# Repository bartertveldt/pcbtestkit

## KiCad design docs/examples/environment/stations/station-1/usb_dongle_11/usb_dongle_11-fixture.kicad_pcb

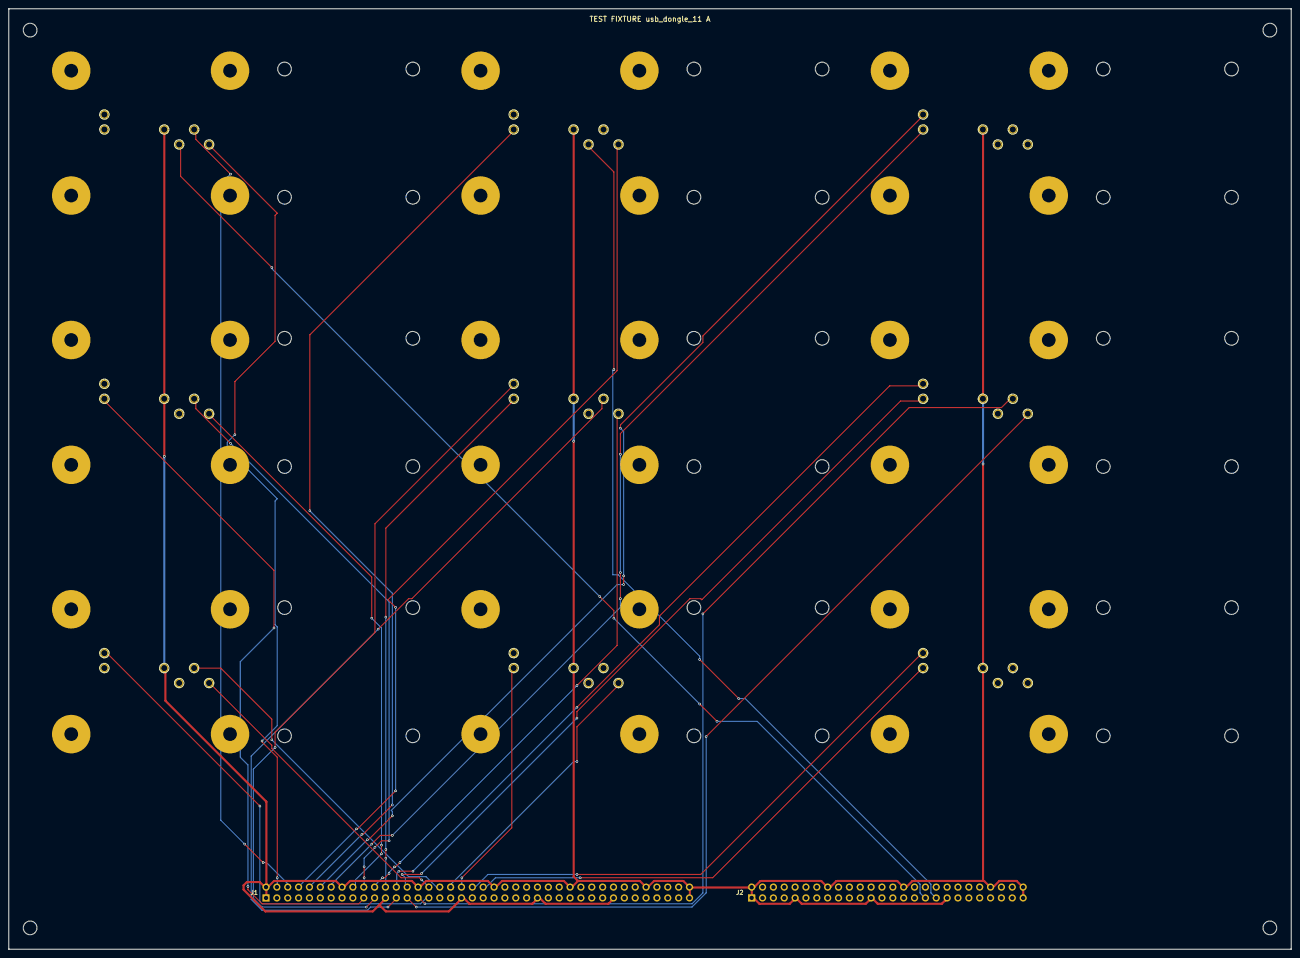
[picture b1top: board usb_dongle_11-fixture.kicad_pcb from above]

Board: 2 copper layers, 300.0 x 220.0 mm, 150 parts (0 on the bottom side), 39 nets.

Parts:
H1, H2, H3, H4: M3; MountingHole_3.2mm
J1: J1; PinHeader_2x40_P2.54mm_Vertical
J2: J2; PinHeader_2x26_P2.54mm_Vertical
K1, K2, K3, K4, K5, K6, K7, K8, K9: TOGGLE CLAMP; ToggleClamp
N1, N2, N3, N4, N5, N6, N7, N8, N9: NEST; Nest
NK1, NK2, NK3, NK4, NK5, NK6, NK7, NK8, NK9, NK10, NK11, NK12, NK13, NK14, NK15, NK16, NK17, NK18, NK19, NK20, NK21, NK22, NK23, NK24, NK25, NK26, NK27, NK28, NK29, NK30, NK31, NK32, NK33, NK34, NK35, NK36: CLAMP M3; ClampScrew_M3
NP1, NP2, NP3, NP4, NP5, NP6, NP7, NP8, NP9, NP10, NP11, NP12, NP13, NP14, NP15, NP16, NP17, NP18, NP19, NP20, NP21, NP22, NP23, NP24, NP25, NP26, NP27, NP28, NP29, NP30, NP31, NP32, NP33, NP34, NP35, NP36: STANDOFF M3; NestPost_M3
P1, P7, P13, P19, P25, P31, P37, P43, P49: GND; Pogo_P75_receptacle
P2, P8, P14, P20, P26, P32, P38, P44, P50: +3V3; Pogo_P75_receptacle
P3, P9, P15, P21, P27, P33, P39, P45, P51: VBUS; Pogo_P75_receptacle
P4, P10, P16, P22, P28, P34, P40, P46, P52: SWCLK; Pogo_P75_receptacle
P5, P11, P17, P23, P29, P35, P41, P47, P53: SWDIO; Pogo_P75_receptacle
P6, P12, P18, P24, P30, P36, P42, P48, P54: USB_D+; Pogo_P75_receptacle

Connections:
GND: J1.1 (GND), J1.2 (GND), J1.9 (GND), J1.16 (GND), J1.23 (GND), J1.30 (GND), J1.37 (GND), J1.44 (GND), J1.51 (GND), J1.58 (GND), J1.65 (GND), J1.72 (GND), J1.79 (GND), J1.80 (GND), J2.1 (GND), J2.2 (GND), J2.9 (GND), J2.16 (GND), J2.23 (GND), J2.30 (GND), J2.37 (GND), J2.46 (GND), J2.51 (GND), J2.52 (GND), P1.1, P7.1, P13.1, P19.1, P25.1, P31.1, P37.1, P43.1, P49.1
S1_TP_+3V3: J1.3 (AIN1), P2.1
S1_TP_SWCLK: J1.5 (AIN3), P4.1
S1_TP_SWDIO: J1.6 (AIN4), P5.1
S1_TP_USB_D+: J2.33 (USB_DP), P6.1
S1_TP_VBUS: J1.4 (AIN2), P3.1
S2_TP_+3V3: J1.7 (AIN5), P8.1
S2_TP_SWCLK: J1.10 (AIN7), P10.1
S2_TP_SWDIO: J1.11 (AIN8), P11.1
S2_TP_USB_D+: J2.35 (USB2_DP), P12.1
S2_TP_VBUS: J1.8 (AIN6), P9.1
S3_TP_+3V3: J1.12 (AIN9), P14.1
S3_TP_SWCLK: J1.14 (AIN11), P16.1
S3_TP_SWDIO: J1.15 (AIN12), P17.1
S3_TP_VBUS: J1.13 (AIN10), P15.1
S4_TP_+3V3: J1.17 (AIN13), P20.1
S4_TP_SWCLK: J1.19 (AIN15), P22.1
S4_TP_SWDIO: J1.20 (AIN16), P23.1
S4_TP_VBUS: J1.18 (AIN14), P21.1
S5_TP_+3V3: J1.21 (AIN17), P26.1
S5_TP_SWCLK: J1.24 (AIN19), P28.1
S5_TP_SWDIO: J1.25 (AIN20), P29.1
S5_TP_VBUS: J1.22 (AIN18), P27.1
S6_TP_+3V3: J1.26 (AIN21), P32.1
S6_TP_SWCLK: J1.28 (AIN23), P34.1
S6_TP_SWDIO: J1.29 (AIN24), P35.1
S6_TP_VBUS: J1.27 (AIN22), P33.1
S7_TP_+3V3: J1.31 (AIN25), P38.1
S7_TP_SWCLK: J1.33 (AIN27), P40.1
S7_TP_SWDIO: J1.34 (AIN28), P41.1
S7_TP_VBUS: J1.32 (AIN26), P39.1
S8_TP_+3V3: J1.35 (AIN29), P44.1
S8_TP_SWCLK: J1.38 (AIN31), P46.1
S8_TP_SWDIO: J1.39 (AIN32), P47.1
S8_TP_VBUS: J1.36 (AIN30), P45.1
S9_TP_+3V3: J1.40 (AIN33), P50.1
S9_TP_SWCLK: J1.42 (AIN35), P52.1
S9_TP_SWDIO: J1.43 (AIN36), P53.1
S9_TP_VBUS: J1.41 (AIN34), P51.1

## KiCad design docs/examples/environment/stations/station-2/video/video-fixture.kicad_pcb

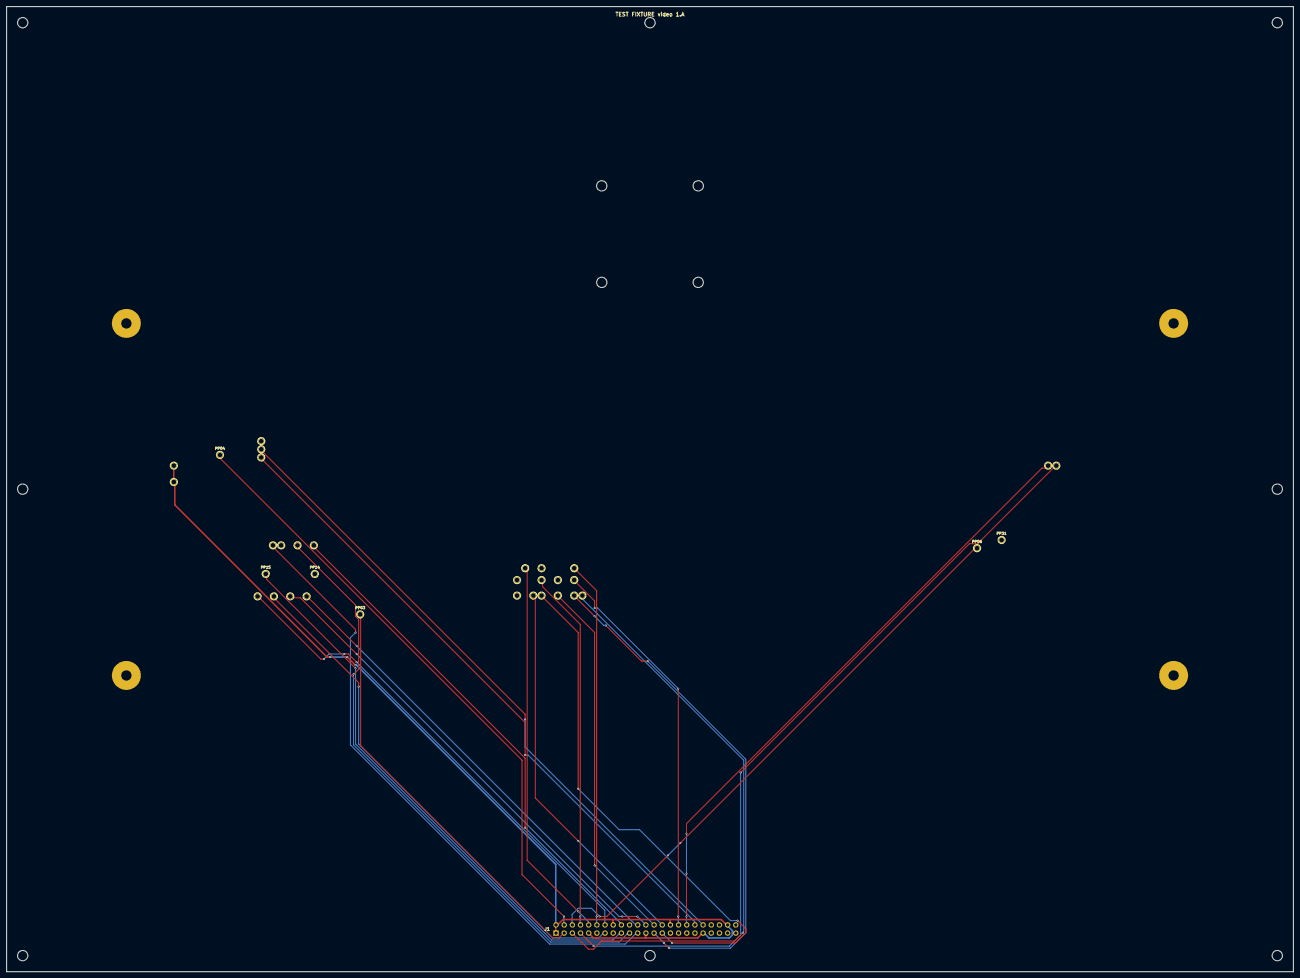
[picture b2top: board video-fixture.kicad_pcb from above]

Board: 2 copper layers, 400.0 x 300.0 mm, 53 parts (0 on the bottom side), 33 nets.

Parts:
H1, H2, H3, H4, H5, H6, H7, H8: M3; MountingHole_3.2mm
J1: J1; PinHeader_2x23_P2.54mm_Vertical
K1: TOGGLE CLAMP; ToggleClamp
N1: NEST; Nest
NK1, NK2, NK3, NK4: CLAMP M3; ClampScrew_M3
NP1, NP2, NP3, NP4: STANDOFF M3; NestPost_M3
P1, P2: GND; Pogo_P75_receptacle
P3: +3.3V; Pogo_P75_receptacle
P4: +5F; Pogo_P75_receptacle
P5: +5V; Pogo_P75_receptacle
P6: VAA; Pogo_P75_receptacle
P7: BLANK-; Pogo_P75_receptacle
P8: EA1; Pogo_P75_receptacle
P9: EA2; Pogo_P75_receptacle
P10: EA3; Pogo_P75_receptacle
P11: EA4; Pogo_P75_receptacle
P12: EA5; Pogo_P75_receptacle
P13: EA6; Pogo_P75_receptacle
P14: EA7; Pogo_P75_receptacle
P15: EA9; Pogo_P75_receptacle
P16: EA10; Pogo_P75_receptacle
P17: EA11; Pogo_P75_receptacle
P18: EA12; Pogo_P75_receptacle
P19: EA13; Pogo_P75_receptacle
P20: EA14; Pogo_P75_receptacle
P21: EA15; Pogo_P75_receptacle
P22: EQ0; Pogo_P75_receptacle
P23: EQ1; Pogo_P75_receptacle
P24: EQ2; Pogo_P75_receptacle
P25: EQ3; Pogo_P75_receptacle
P26: EQ4; Pogo_P75_receptacle
P27: EQ5; Pogo_P75_receptacle
P28: EQ6; Pogo_P75_receptacle
P29: EQ7; Pogo_P75_receptacle
P30: CLKCDA; Pogo_P75_receptacle
P31: CSYNCIN-; Pogo_P75_receptacle
P32: DQ8; Pogo_P75_receptacle
P33: DQ9; Pogo_P75_receptacle
P34: DQ10; Pogo_P75_receptacle

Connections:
GND: J1.1 (GND), J1.2 (GND), J1.9 (GND), J1.16 (GND), J1.23 (GND), J1.30 (GND), J1.37 (GND), J1.44 (GND), J1.45 (GND), P1.1, P2.1
TP_+3.3V: J1.3 (AIN1), P3.1
TP_+5F: J1.4 (AIN2), P4.1
TP_+5V: J1.5 (AIN3), P5.1
TP_BLANK-: J1.7 (AIN5), P7.1
TP_CLKCDA: J1.34 (AIN28), P30.1
TP_CSYNCIN-: J1.35 (AIN29), P31.1
TP_DQ8: J1.36 (AIN30), P32.1
TP_DQ9: J1.38 (AIN31), P33.1
TP_DQ10: J1.39 (AIN32), P34.1
TP_EA1: J1.8 (AIN6), P8.1
TP_EA2: J1.10 (AIN7), P9.1
TP_EA3: J1.11 (AIN8), P10.1
TP_EA4: J1.12 (AIN9), P11.1
TP_EA5: J1.13 (AIN10), P12.1
TP_EA6: J1.14 (AIN11), P13.1
TP_EA7: J1.15 (AIN12), P14.1
TP_EA9: J1.17 (AIN13), P15.1
TP_EA10: J1.18 (AIN14), P16.1
TP_EA11: J1.19 (AIN15), P17.1
TP_EA12: J1.20 (AIN16), P18.1
TP_EA13: J1.21 (AIN17), P19.1
TP_EA14: J1.22 (AIN18), P20.1
TP_EA15: J1.24 (AIN19), P21.1
TP_EQ0: J1.25 (AIN20), P22.1
TP_EQ1: J1.26 (AIN21), P23.1
TP_EQ2: J1.27 (AIN22), P24.1
TP_EQ3: J1.28 (AIN23), P25.1
TP_EQ4: J1.29 (AIN24), P26.1
TP_EQ5: J1.31 (AIN25), P27.1
TP_EQ6: J1.32 (AIN26), P28.1
TP_EQ7: J1.33 (AIN27), P29.1
TP_VAA: J1.6 (AIN4), P6.1

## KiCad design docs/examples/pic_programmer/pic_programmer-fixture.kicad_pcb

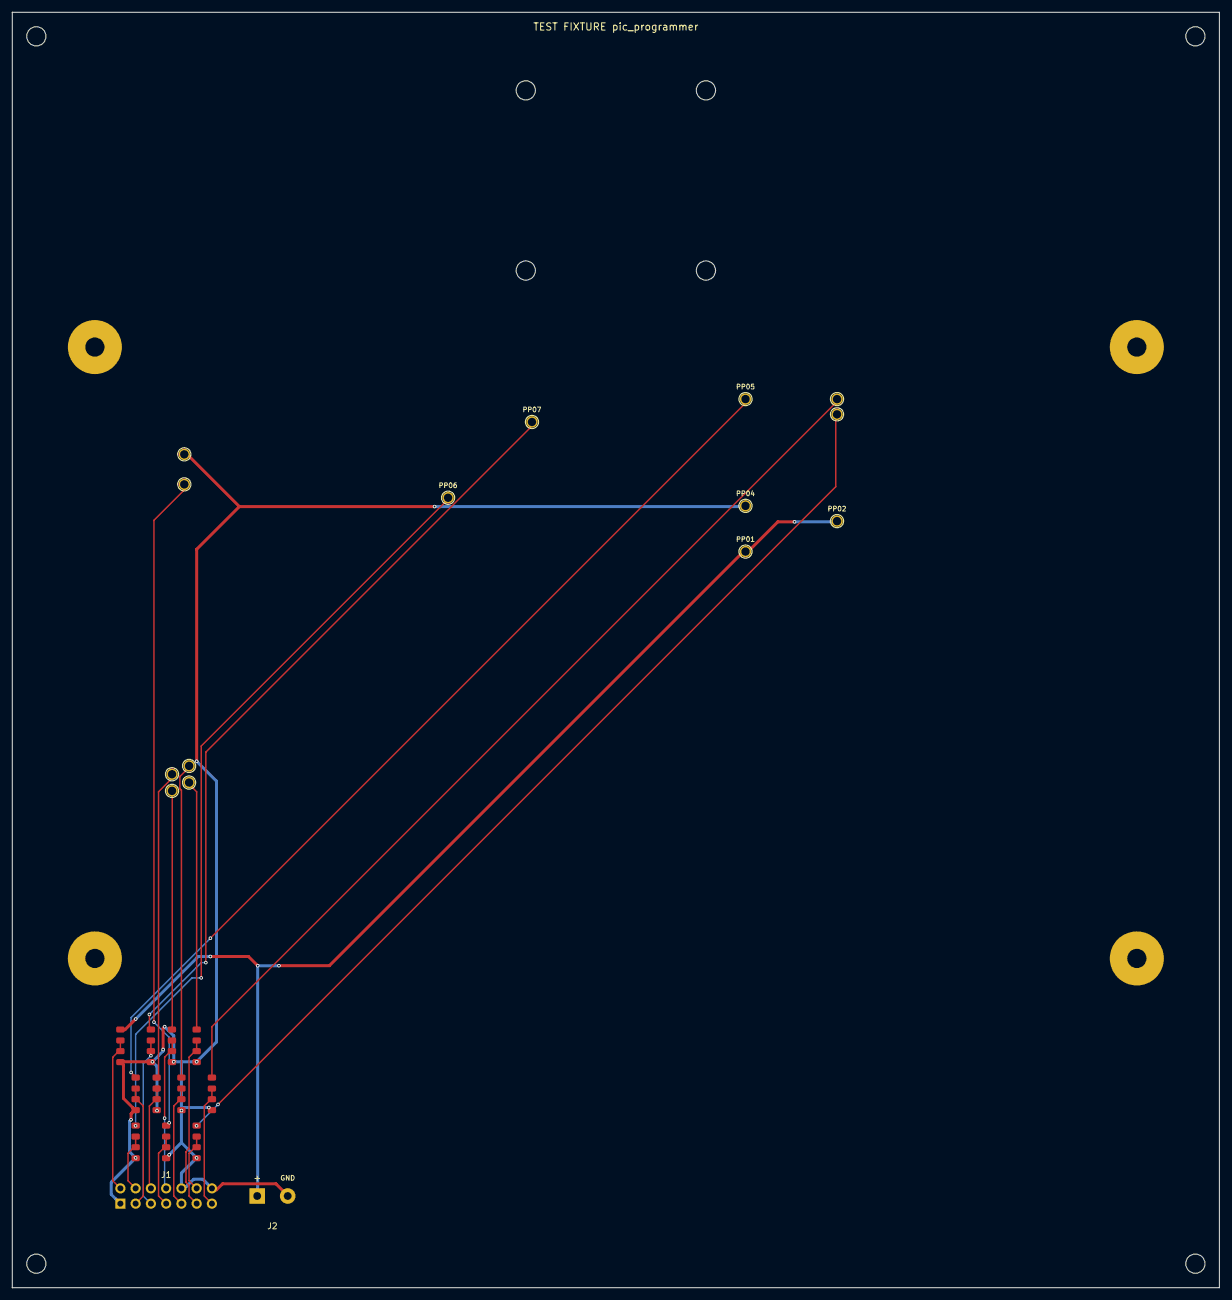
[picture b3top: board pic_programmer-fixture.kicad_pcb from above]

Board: 2 copper layers, 201.0 x 212.4 mm, 52 parts (0 on the bottom side), 23 nets.

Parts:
H1, H2, H3, H4: M3 standoff; MountingHole_3.2mm
J1: TEST_IO; PinHeader_2x07_P2.54mm_Vertical
J2: DUT_POWER; TerminalBlock_bornier-2_P5.08mm
K1: TOGGLE CLAMP; ToggleClamp
N1: NEST; Nest
NK1, NK2, NK3, NK4: CLAMP M3; ClampScrew_M3
NP1, NP2, NP3, NP4: STANDOFF M3; NestPost_M3
P1, P2: VCC_PIC; Pogo_P75_receptacle
P3, P4: GND; Pogo_P75_receptacle
P5: VPP{slash}MCLR; Pogo_P75_receptacle
P6: VCC; Pogo_P75_receptacle
P7: VPP; Pogo_P75_receptacle
P8: PC-DATA-IN; Pogo_P75_receptacle
P9: Net-(D1-A); Pogo_P75_receptacle
P10: PC-CLOCK-OUT; Pogo_P75_receptacle
P11: PC-DATA-OUT; Pogo_P75_receptacle
P12: VPP_ON; Pogo_P75_receptacle
P13: CLOCK-RB6; Pogo_P75_receptacle
P14: DATA-RB7; Pogo_P75_receptacle
R1, R3, R5, R7: 1.2k; R_0805_2012Metric
R2, R4, R6, R8: 10k; R_0805_2012Metric
R9, R11, R13, R15, R17, R19, R21: 12k; R_0805_2012Metric
R10, R12, R14, R16, R18, R20, R22: 100k; R_0805_2012Metric

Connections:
CH01: J1.2 (CH01), R1.1, R2.2
CH02: J1.3 (CH02), R3.1, R4.2
CH03: J1.4 (CH03), R5.1, R6.2
CH04: J1.5 (CH04), R7.1, R8.2
CH05: J1.6 (CH05), R9.1, R10.2
CH06: J1.7 (CH06), R11.1, R12.2
CH07: J1.8 (CH07), R13.1, R14.2
CH08: J1.9 (CH08), R15.1, R16.2
CH09: J1.11 (CH09), R17.1, R18.2
CH10: J1.12 (CH10), R19.1, R20.2
CH11: J1.13 (CH11), R21.1, R22.2
GND: J1.1 (GND), J1.10 (GND), J1.14 (GND), J2.2 (GND), P3.1, P4.1, R2.1, R4.1, R6.1, R8.1, R10.1, R12.1, R14.1, R16.1, R18.1, R20.1, R22.1
TP_CLOCK-RB6: P13.1, R19.2
TP_DATA-RB7: P14.1, R21.2
TP_Net-_D1-A: P9.1, R11.2
TP_PC-CLOCK-OUT: P10.1, R13.2
TP_PC-DATA-IN: P8.1, R9.2
TP_PC-DATA-OUT: P11.1, R15.2
TP_VCC: P6.1, R5.2
TP_VPP: P7.1, R7.2
TP_VPP_ON: P12.1, R17.2
TP_VPP_slash_MCLR: P5.1, R3.2
VIN: J2.1 (VIN), P1.1, P2.1, R1.2

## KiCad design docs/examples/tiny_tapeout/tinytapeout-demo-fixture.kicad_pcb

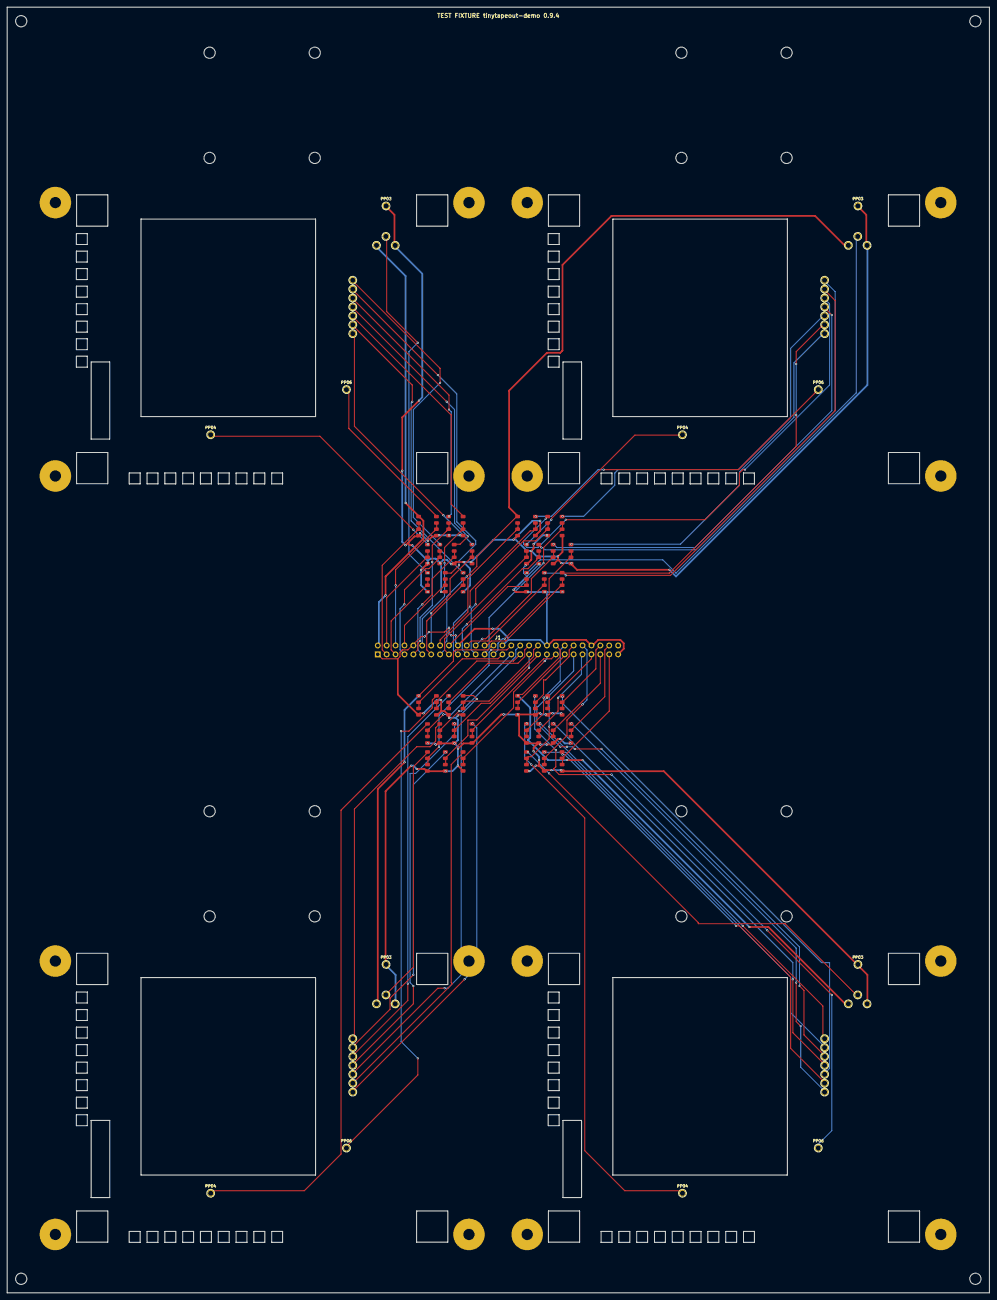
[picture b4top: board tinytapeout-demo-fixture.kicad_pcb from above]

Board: 2 copper layers, 280.2 x 366.8 mm, 185 parts (0 on the bottom side), 89 nets.

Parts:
H1, H2, H3, H4: M3 standoff; MountingHole_3.2mm
J1: TEST_IO; PinHeader_2x28_P2.54mm_Vertical
K1, K2, K3, K4: TOGGLE CLAMP; ToggleClamp
N1, N2, N3, N4: NEST; Nest
NK1, NK2, NK3, NK4, NK5, NK6, NK7, NK8, NK9, NK10, NK11, NK12, NK13, NK14, NK15, NK16: CLAMP M3; ClampScrew_M3
NP1, NP2, NP3, NP4, NP5, NP6, NP7, NP8, NP9, NP10, NP11, NP12, NP13, NP14, NP15, NP16: STANDOFF M3; NestPost_M3
P1, P14, P27, P40: VBUS; Pogo_P75_receptacle
P2, P3, P15, P16, P28, P29, P41, P42: GND; Pogo_P75_receptacle
P4, P17, P30, P43: +3V3; Pogo_P75_receptacle
P5, P18, P31, P44: +5V; Pogo_P75_receptacle
P6, P19, P32, P45: DVDD; Pogo_P75_receptacle
P7, P20, P33, P46: in1; Pogo_P75_receptacle
P8, P21, P34, P47: in2; Pogo_P75_receptacle
P9, P22, P35, P48: in3; Pogo_P75_receptacle
P10, P23, P36, P49: in4; Pogo_P75_receptacle
P11, P24, P37, P50: in5; Pogo_P75_receptacle
P12, P25, P38, P51: in6; Pogo_P75_receptacle
P13, P26, P39, P52: in7; Pogo_P75_receptacle
R1, R5, R7, R23, R27, R29, R45, R49, R51, R67, R71, R73: 8.2k; R_0805_2012Metric
R2, R4, R6, R8, R24, R26, R28, R30, R46, R48, R50, R52, R68, R70, R72, R74: 10k; R_0805_2012Metric
R3, R25, R47, R69: 1.8k; R_0805_2012Metric
R9, R11, R13, R15, R17, R19, R21, R31, R33, R35, R37, R39, R41, R43, R53, R55, R57, R59, R61, R63, R65, R75, R77, R79, R81, R83, R85, R87: 82k; R_0805_2012Metric
R10, R12, R14, R16, R18, R20, R22, R32, R34, R36, R38, R40, R42, R44, R54, R56, R58, R60, R62, R64, R66, R76, R78, R80, R82, R84, R86, R88: 100k; R_0805_2012Metric

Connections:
GND: J1.1 (GND), J1.10 (GND), J1.20 (GND), J1.30 (GND), J1.40 (GND), J1.50 (GND), J1.55 (GND), P2.1, P3.1, P15.1, P16.1, P28.1, P29.1, P41.1, P42.1, R2.1, R4.1, R6.1, R8.1, R10.1, R12.1, R14.1, R16.1, R18.1, R20.1, R22.1, R24.1, R26.1, R28.1, R30.1, R32.1, R34.1, R36.1, R38.1, R40.1, R42.1, R44.1, R46.1, R48.1, R50.1, R52.1, R54.1, R56.1, R58.1, R60.1, R62.1, R64.1, R66.1, R68.1, R70.1, R72.1, R74.1, R76.1, R78.1, R80.1, R82.1, R84.1, R86.1, R88.1
S1_CH01: J1.3 (S1 CH01), R1.1, R2.2
S1_CH02: J1.4 (S1 CH02), R3.1, R4.2
S1_CH03: J1.5 (S1 CH03), R5.1, R6.2
S1_CH04: J1.6 (S1 CH04), R7.1, R8.2
S1_CH05: J1.7 (S1 CH05), R9.1, R10.2
S1_CH06: J1.8 (S1 CH06), R11.1, R12.2
S1_CH07: J1.9 (S1 CH07), R13.1, R14.2
S1_CH08: J1.11 (S1 CH08), R15.1, R16.2
S1_CH09: J1.12 (S1 CH09), R17.1, R18.2
S1_CH10: J1.13 (S1 CH10), R19.1, R20.2
S1_CH11: J1.14 (S1 CH11), R21.1, R22.2
S1_TP_+3V3: P4.1, R3.2
S1_TP_+5V: P5.1, R5.2
S1_TP_DVDD: P6.1, R7.2
S1_TP_in1: P7.1, R9.2
S1_TP_in2: P8.1, R11.2
S1_TP_in3: P9.1, R13.2
S1_TP_in4: P10.1, R15.2
S1_TP_in5: P11.1, R17.2
S1_TP_in6: P12.1, R19.2
S1_TP_in7: P13.1, R21.2
S1_VIN: J1.2 (S1 VIN), P1.1, R1.2
S2_CH01: J1.16 (S2 CH01), R23.1, R24.2
S2_CH02: J1.17 (S2 CH02), R25.1, R26.2
S2_CH03: J1.18 (S2 CH03), R27.1, R28.2
S2_CH04: J1.19 (S2 CH04), R29.1, R30.2
S2_CH05: J1.21 (S2 CH05), R31.1, R32.2
S2_CH06: J1.22 (S2 CH06), R33.1, R34.2
S2_CH07: J1.23 (S2 CH07), R35.1, R36.2
S2_CH08: J1.24 (S2 CH08), R37.1, R38.2
S2_CH09: J1.25 (S2 CH09), R39.1, R40.2
S2_CH10: J1.26 (S2 CH10), R41.1, R42.2
S2_CH11: J1.27 (S2 CH11), R43.1, R44.2
S2_TP_+3V3: P17.1, R25.2
S2_TP_+5V: P18.1, R27.2
S2_TP_DVDD: P19.1, R29.2
S2_TP_in1: P20.1, R31.2
S2_TP_in2: P21.1, R33.2
S2_TP_in3: P22.1, R35.2
S2_TP_in4: P23.1, R37.2
S2_TP_in5: P24.1, R39.2
S2_TP_in6: P25.1, R41.2
S2_TP_in7: P26.1, R43.2
S2_VIN: J1.15 (S2 VIN), P14.1, R23.2
S3_CH01: J1.29 (S3 CH01), R45.1, R46.2
S3_CH02: J1.31 (S3 CH02), R47.1, R48.2
S3_CH03: J1.32 (S3 CH03), R49.1, R50.2
S3_CH04: J1.33 (S3 CH04), R51.1, R52.2
S3_CH05: J1.34 (S3 CH05), R53.1, R54.2
S3_CH06: J1.35 (S3 CH06), R55.1, R56.2
S3_CH07: J1.36 (S3 CH07), R57.1, R58.2
S3_CH08: J1.37 (S3 CH08), R59.1, R60.2
S3_CH09: J1.38 (S3 CH09), R61.1, R62.2
S3_CH10: J1.39 (S3 CH10), R63.1, R64.2
S3_CH11: J1.41 (S3 CH11), R65.1, R66.2
S3_TP_+3V3: P30.1, R47.2
S3_TP_+5V: P31.1, R49.2
S3_TP_DVDD: P32.1, R51.2
S3_TP_in1: P33.1, R53.2
S3_TP_in2: P34.1, R55.2
S3_TP_in3: P35.1, R57.2
S3_TP_in4: P36.1, R59.2
S3_TP_in5: P37.1, R61.2
S3_TP_in6: P38.1, R63.2
S3_TP_in7: P39.1, R65.2
S3_VIN: J1.28 (S3 VIN), P27.1, R45.2
S4_CH01: J1.43 (S4 CH01), R67.1, R68.2
S4_CH02: J1.44 (S4 CH02), R69.1, R70.2
S4_CH03: J1.45 (S4 CH03), R71.1, R72.2
S4_CH04: J1.46 (S4 CH04), R73.1, R74.2
S4_CH05: J1.47 (S4 CH05), R75.1, R76.2
S4_CH06: J1.48 (S4 CH06), R77.1, R78.2
S4_CH07: J1.49 (S4 CH07), R79.1, R80.2
S4_CH08: J1.51 (S4 CH08), R81.1, R82.2
S4_CH09: J1.52 (S4 CH09), R83.1, R84.2
S4_CH10: J1.53 (S4 CH10), R85.1, R86.2
S4_CH11: J1.54 (S4 CH11), R87.1, R88.2
S4_TP_+3V3: P43.1, R69.2
S4_TP_+5V: P44.1, R71.2
S4_TP_DVDD: P45.1, R73.2
S4_TP_in1: P46.1, R75.2
S4_TP_in2: P47.1, R77.2
S4_TP_in3: P48.1, R79.2
S4_TP_in4: P49.1, R81.2
S4_TP_in5: P50.1, R83.2
S4_TP_in6: P51.1, R85.2
S4_TP_in7: P52.1, R87.2
S4_VIN: J1.42 (S4 VIN), P40.1, R67.2
